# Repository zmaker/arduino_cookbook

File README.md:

# arduino_cookbook
gli sketch del nuovo progetto Arduino Cookbook e dei video di YouTube

La pagina con i video: 
http://www.zeppelinmaker.it/arduino100/

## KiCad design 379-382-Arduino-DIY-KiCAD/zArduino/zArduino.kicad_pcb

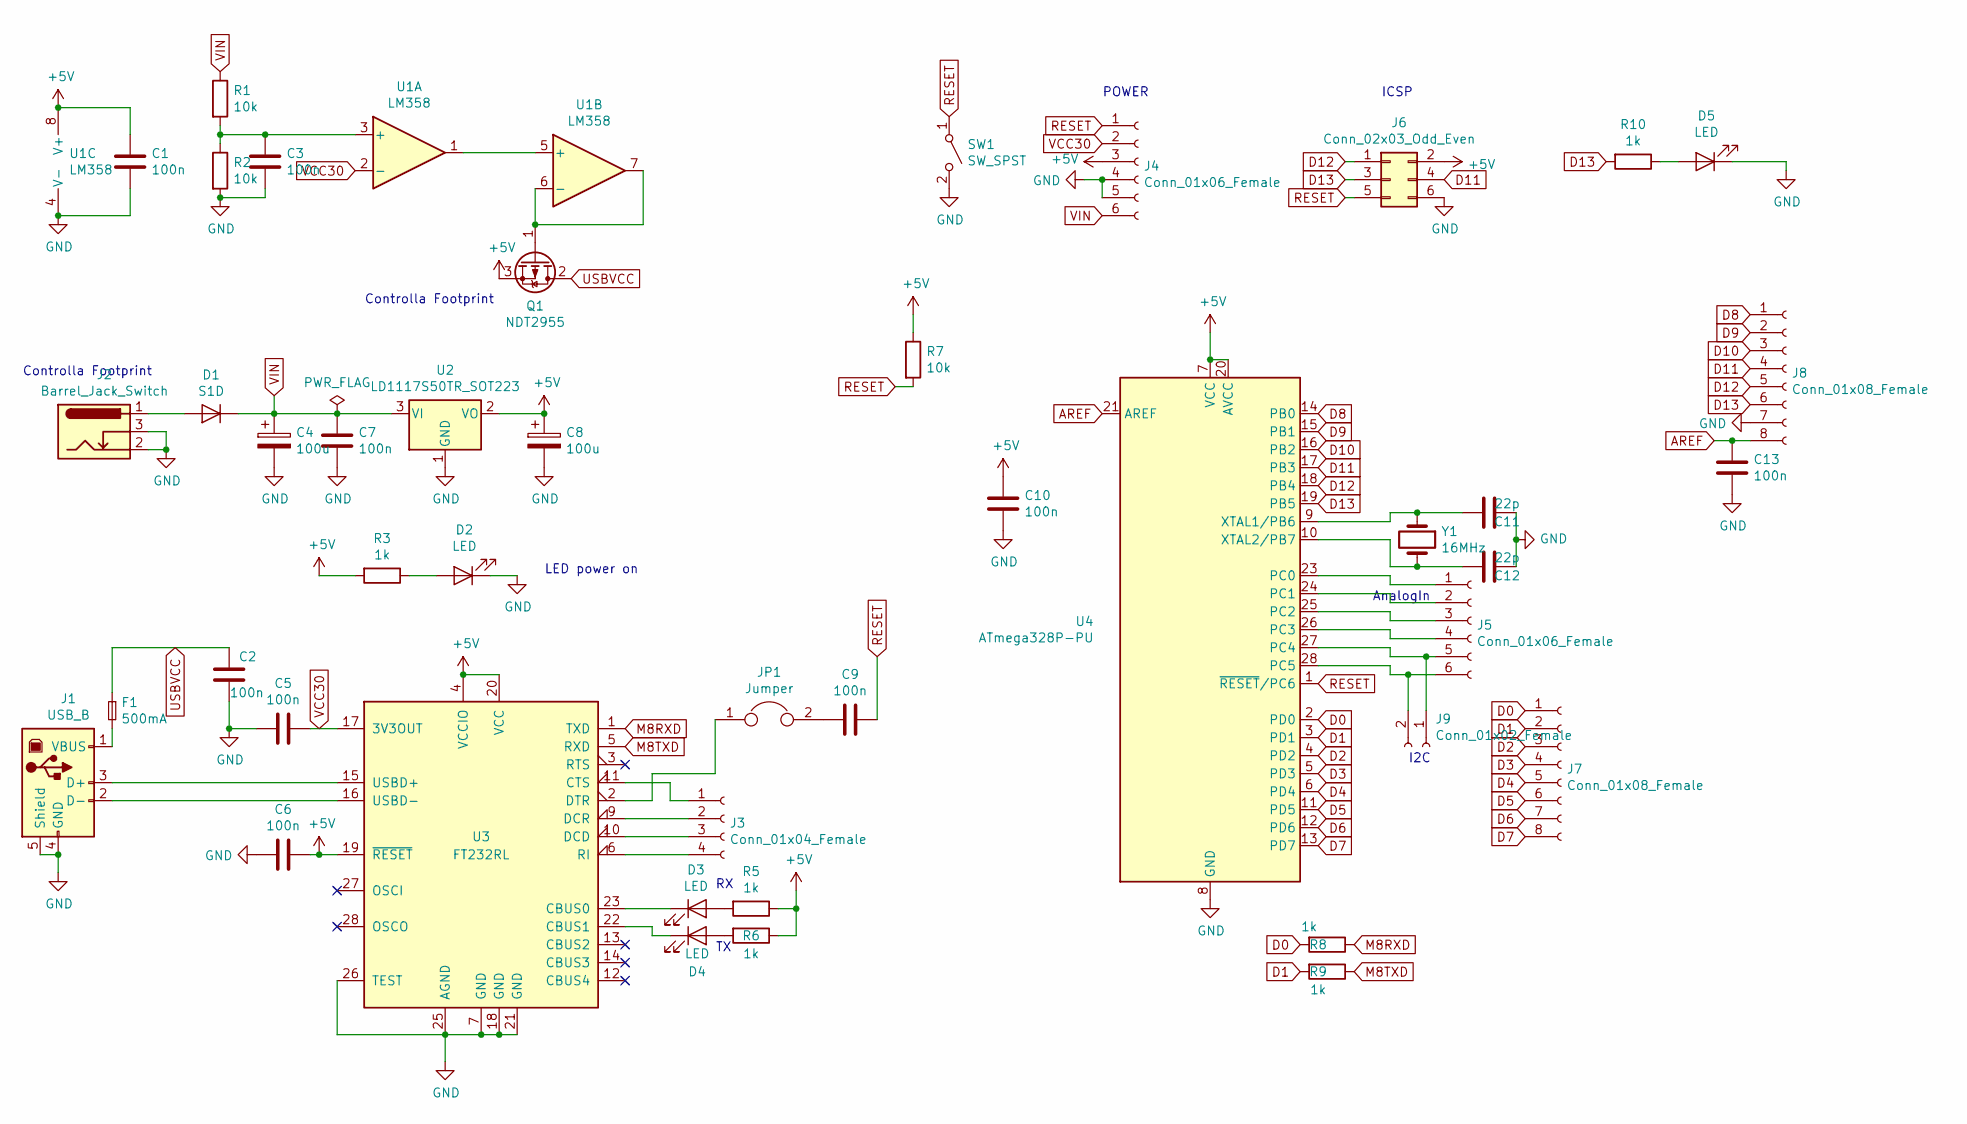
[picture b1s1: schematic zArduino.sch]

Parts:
C1, C2, C3, C5, C6, C7, C9, C10, C13: 100n; C_0805_2012Metric_Pad1.15x1.40mm_HandSolder
C4, C8: 100u; CP_Elec_8x6.2
C11, C12: 22p; C_0805_2012Metric_Pad1.15x1.40mm_HandSolder
D1: S1D; D_SMA_Handsoldering
D2, D3, D4, D5: LED; LED_1206_3216Metric_Pad1.42x1.75mm_HandSolder
F1: 500mA; Fuse_1206_3216Metric_Pad1.42x1.75mm_HandSolder
J1: USB_B; USB_B_OST_USB-B1HSxx_Horizontal
J2: Barrel_Jack_Switch; BarrelJack_Wuerth_6941xx301002
J3: Conn_01x04_Female; PinHeader_1x04_P2.54mm_Vertical
J4, J5: Conn_01x06_Female; PinHeader_1x06_P2.54mm_Vertical
J6: Conn_02x03_Odd_Even; PinHeader_2x03_P2.54mm_Vertical
J7, J8: Conn_01x08_Female; PinHeader_1x08_P2.54mm_Vertical
J9: Conn_01x02_Female; PinHeader_1x02_P2.54mm_Vertical
JP1: Jumper; PinHeader_1x02_P2.54mm_Vertical
Q1: NDT2955; SOT-223-3_TabPin2
R1, R2, R7: 10k; R_0805_2012Metric_Pad1.15x1.40mm_HandSolder
R3, R5, R6, R8, R9, R10: 1k; R_0805_2012Metric_Pad1.15x1.40mm_HandSolder
SW1: SW_SPST; SW_Push_1P1T_NO_CK_KSC7xxJ
U1: LM358; SOIC-8_5.275x5.275mm_P1.27mm
U2: LD1117S50TR_SOT223; TO-252-2
U3: FT232RL; SSOP-28_5.3x10.2mm_P0.65mm
U4: ATmega328P-PU; DIP-28_W7.62mm
Y1: 16MHz; Crystal_SMD_HC49-SD

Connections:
+5V: C1.1, C6.1, C8.1, C10.1, J4.3, J6.2, Q1.3 (S), R3.2, R5.1, R6.1, R7.1, U1.8 (V+), U2.2 (VO), U3.4 (VCCIO), U3.19 (~RESET~), U3.20 (VCC), U4.7 (VCC), U4.20 (AVCC)
AREF: C13.1, J8.8, U4.21 (AREF)
D0: J7.1, R8.2, U4.2 (PD0)
D1: J7.2, R9.2, U4.3 (PD1)
D2: J7.3, U4.4 (PD2)
D3: J7.4, U4.5 (PD3)
D4: J7.5, U4.6 (PD4)
D5: J7.6, U4.11 (PD5)
D6: J7.7, U4.12 (PD6)
D7: J7.8, U4.13 (PD7)
D8: J8.1, U4.14 (PB0)
D9: J8.2, U4.15 (PB1)
D10: J8.3, U4.16 (PB2)
D11: J6.4, J8.4, U4.17 (PB3)
D12: J6.1, J8.5, U4.18 (PB4)
D13: J6.3, J8.6, R10.2, U4.19 (PB5)
GND: C1.2, C2.2, C3.2, C4.2, C5.2, C6.2, C7.2, C8.2, C10.2, C11.1, C12.1, C13.2, D2.1 (K), D5.1 (K), J1.4 (GND), J1.5 (Shield), J2.2, J2.3, J4.4, J4.5, J6.6, J8.7, R2.2, SW1.2 (B), U1.4 (V-), U2.1 (GND), U3.7 (GND), U3.18 (GND), U3.21 (GND), U3.25 (AGND), U3.26 (TEST), U4.8 (GND), U4.22 (GND)
M8RXD: R8.1, U3.1 (TXD)
M8TXD: R9.1, U3.5 (RXD)
unnamed: C3.1, R1.2, R2.1, U1.3 (+)
unnamed: C9.2, JP1.2
unnamed: C11.2, U4.9 (XTAL1/PB6), Y1.1
unnamed: C12.2, U4.10 (XTAL2/PB7), Y1.2
unnamed: D1.2 (A), J2.1
unnamed: D2.2 (A), R3.1
unnamed: D3.1 (K), U3.23 (CBUS0)
unnamed: D3.2 (A), R5.2
unnamed: D4.1 (K), U3.22 (CBUS1)
unnamed: D4.2 (A), R6.2
unnamed: D5.2 (A), R10.1
unnamed: F1.2, J1.1 (VBUS)
unnamed: J1.2 (D-), U3.16 (USBD-)
unnamed: J1.3 (D+), U3.15 (USBD+)
unnamed: J3.1, U3.11 (CTS)
unnamed: J3.2, U3.9 (DCR)
unnamed: J3.3, U3.10 (DCD)
unnamed: J3.4, U3.6 (RI)
unnamed: J5.1, U4.23 (PC0)
unnamed: J5.2, U4.24 (PC1)
unnamed: J5.3, U4.25 (PC2)
unnamed: J5.4, U4.26 (PC3)
unnamed: J5.5, J9.1, U4.27 (PC4)
unnamed: J5.6, J9.2, U4.28 (PC5)
unnamed: JP1.1, U3.2 (DTR)
unnamed: Q1.1 (G), U1.6 (-), U1.7
unnamed 45: U3.3 (RTS); also elsewhere on the board
unnamed: U1.1, U1.5 (+)
RESET: C9.1, J4.1, J6.5, R7.2, SW1.1 (A), U4.1 (~RESET~/PC6); also elsewhere on the board
USBVCC: C2.1, F1.1, Q1.2 (D)
VCC30: C5.1, J4.2, U1.2 (-), U3.17 (3V3OUT)
VIN: C4.1, C7.1, D1.1 (K), J4.6, R1.1, U2.3 (VI)

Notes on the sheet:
Controlla Footprint
LED power on
POWER
ICSP
AnalogIn
I2C

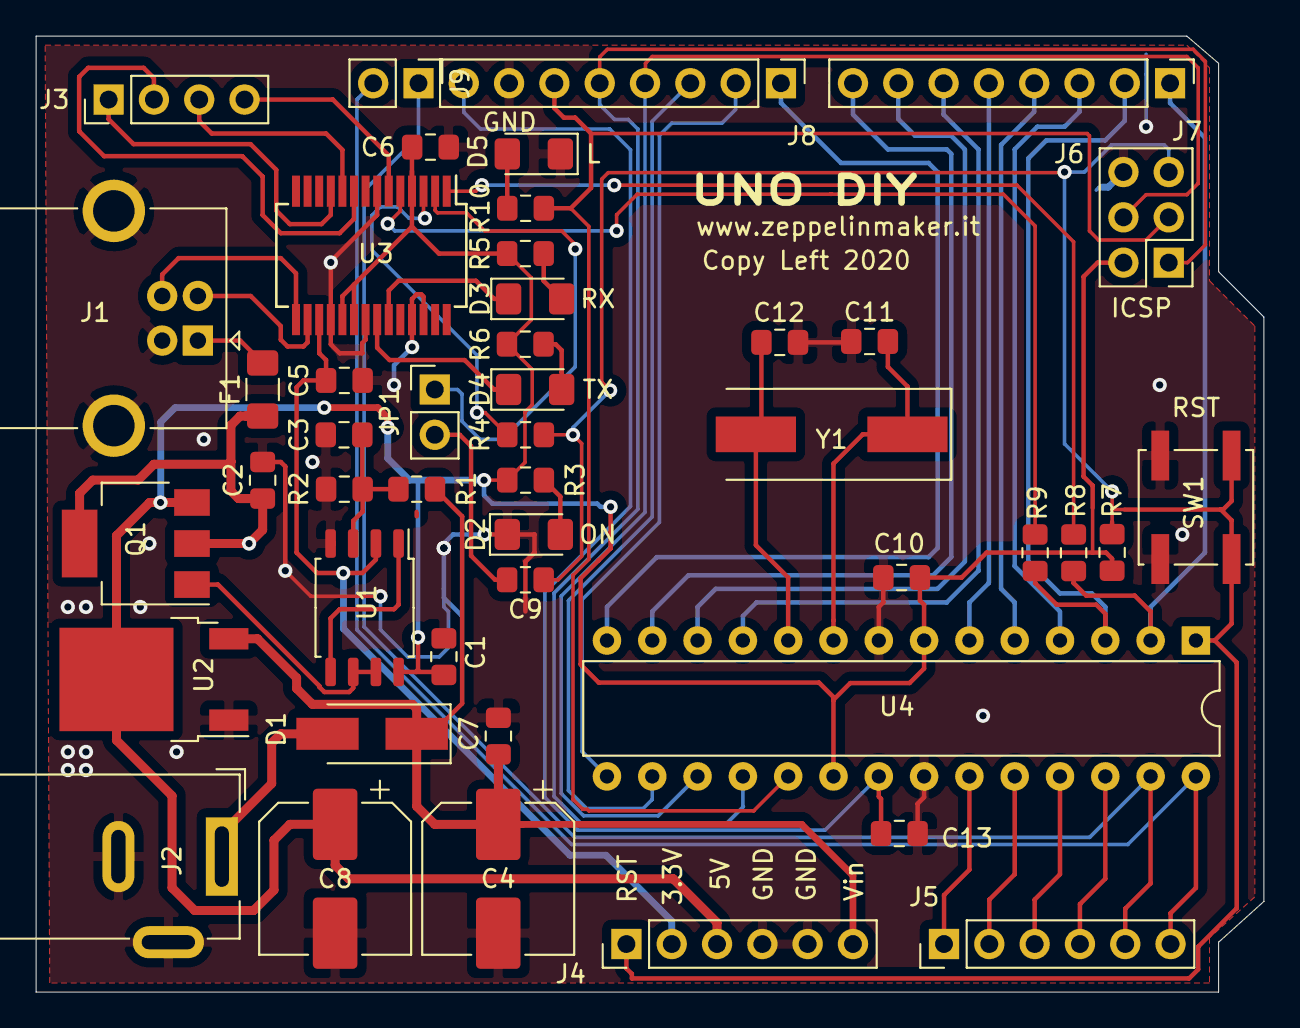
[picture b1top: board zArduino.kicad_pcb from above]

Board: 2 copper layers, 68.8 x 53.6 mm, 46 parts (0 on the bottom side), 51 nets.

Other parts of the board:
R4: 1k; R_0805_2012Metric_Pad1.15x1.40mm_HandSolder

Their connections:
unnamed 45: R4.2; also elsewhere on the board
RESET: R4.1; also elsewhere on the board

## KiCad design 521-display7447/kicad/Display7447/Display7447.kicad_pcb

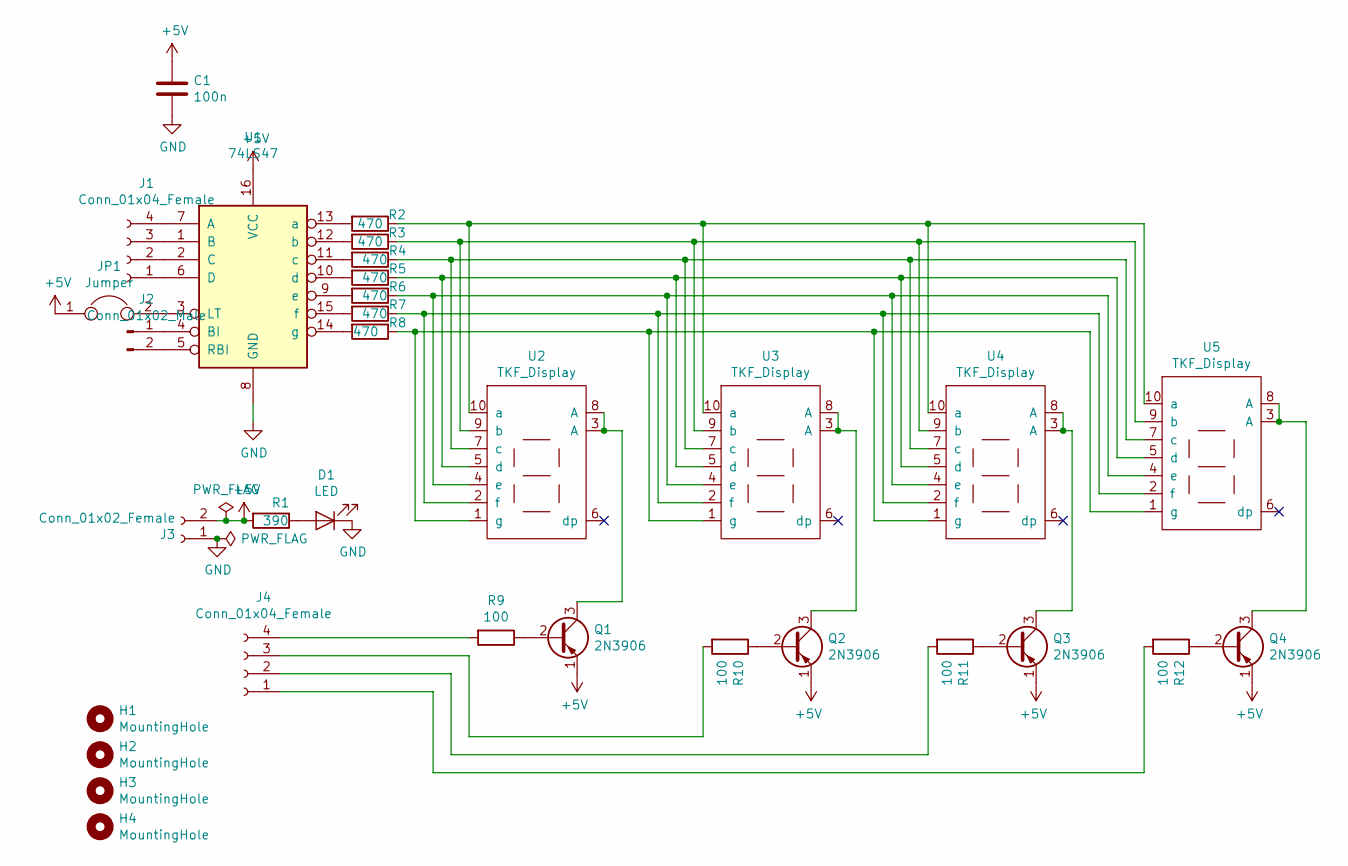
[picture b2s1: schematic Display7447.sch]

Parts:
C1: 100n; C_Disc_D5.0mm_W2.5mm_P2.50mm
D1: LED; LED_D5.0mm
H1, H2, H3, H4: MountingHole; MountingHole_3.2mm_M3
J1, J4: Conn_01x04_Female; PinSocket_1x04_P2.54mm_Vertical
J2: Conn_01x02_Male; PinSocket_1x02_P2.54mm_Vertical
J3: Conn_01x02_Female; PinSocket_1x02_P2.54mm_Vertical
JP1: Jumper; PinSocket_2x01_P2.54mm_Vertical
Q1, Q2, Q3, Q4: 2N3906; TO-92_Inline
R1: 390; R_Axial_DIN0204_L3.6mm_D1.6mm_P7.62mm_Horizontal
R2, R3, R4, R5, R6, R7, R8: 470; R_Axial_DIN0204_L3.6mm_D1.6mm_P7.62mm_Horizontal
R9, R10, R11, R12: 100; R_Axial_DIN0204_L3.6mm_D1.6mm_P7.62mm_Horizontal
U1: 74LS47; DIP-16_W7.62mm_Socket_LongPads
U2, U3, U4, U5: TKF_Display; TFK-Display

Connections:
+5V: C1.1, J3.2, JP1.1, Q1.1 (E), Q2.1 (E), Q3.1 (E), Q4.1 (E), R1.2, U1.16 (VCC)
GND: C1.2, D1.1 (K), J3.1, U1.8 (GND)
unnamed: D1.2 (A), R1.1
unnamed: J1.1, U1.6 (D)
unnamed: J1.2, U1.2 (C)
unnamed: J1.3, U1.1 (B)
unnamed: J1.4, U1.7 (A)
unnamed: J2.1, U1.4 (BI)
unnamed: J2.2, U1.5 (RBI)
unnamed: J4.1, R12.2
unnamed: J4.2, R11.2
unnamed: J4.3, R10.2
unnamed: J4.4, R9.2
unnamed: JP1.2, U1.3 (LT)
unnamed: Q1.2 (B), R9.1
unnamed: Q1.3 (C), U2.3 (A), U2.8 (A)
unnamed: Q2.2 (B), R10.1
unnamed: Q2.3 (C), U3.3 (A), U3.8 (A)
unnamed: Q3.2 (B), R11.1
unnamed: Q3.3 (C), U4.3 (A), U4.8 (A)
unnamed: Q4.2 (B), R12.1
unnamed: Q4.3 (C), U5.3 (A), U5.8 (A)
unnamed: R2.1, U2.10 (a), U3.10 (a), U4.10 (a), U5.10 (a)
unnamed: R2.2, U1.13 (a)
unnamed: R3.1, U2.9 (b), U3.9 (b), U4.9 (b), U5.9 (b)
unnamed: R3.2, U1.12 (b)
unnamed: R4.1, U2.7 (c), U3.7 (c), U4.7 (c), U5.7 (c)
unnamed: R4.2, U1.11 (c)
unnamed: R5.1, U2.5 (d), U3.5 (d), U4.5 (d), U5.5 (d)
unnamed: R5.2, U1.10 (d)
unnamed: R6.1, U2.4 (e), U3.4 (e), U4.4 (e), U5.4 (e)
unnamed: R6.2, U1.9 (e)
unnamed: R7.1, U2.2 (f), U3.2 (f), U4.2 (f), U5.2 (f)
unnamed: R7.2, U1.15 (f)
unnamed: R8.1, U2.1 (g), U3.1 (g), U4.1 (g), U5.1 (g)
unnamed: R8.2, U1.14 (g)

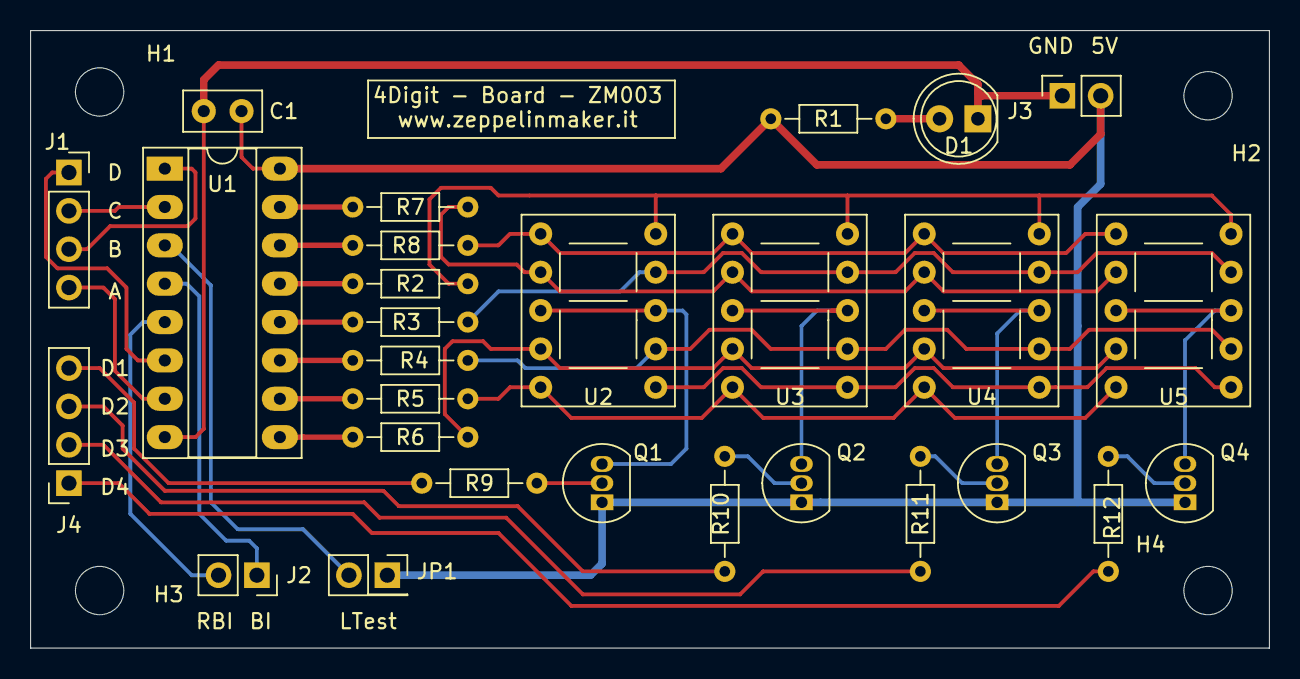
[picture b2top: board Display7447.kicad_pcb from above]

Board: 2 copper layers, 82.0 x 40.9 mm, 32 parts (0 on the bottom side), 36 nets.

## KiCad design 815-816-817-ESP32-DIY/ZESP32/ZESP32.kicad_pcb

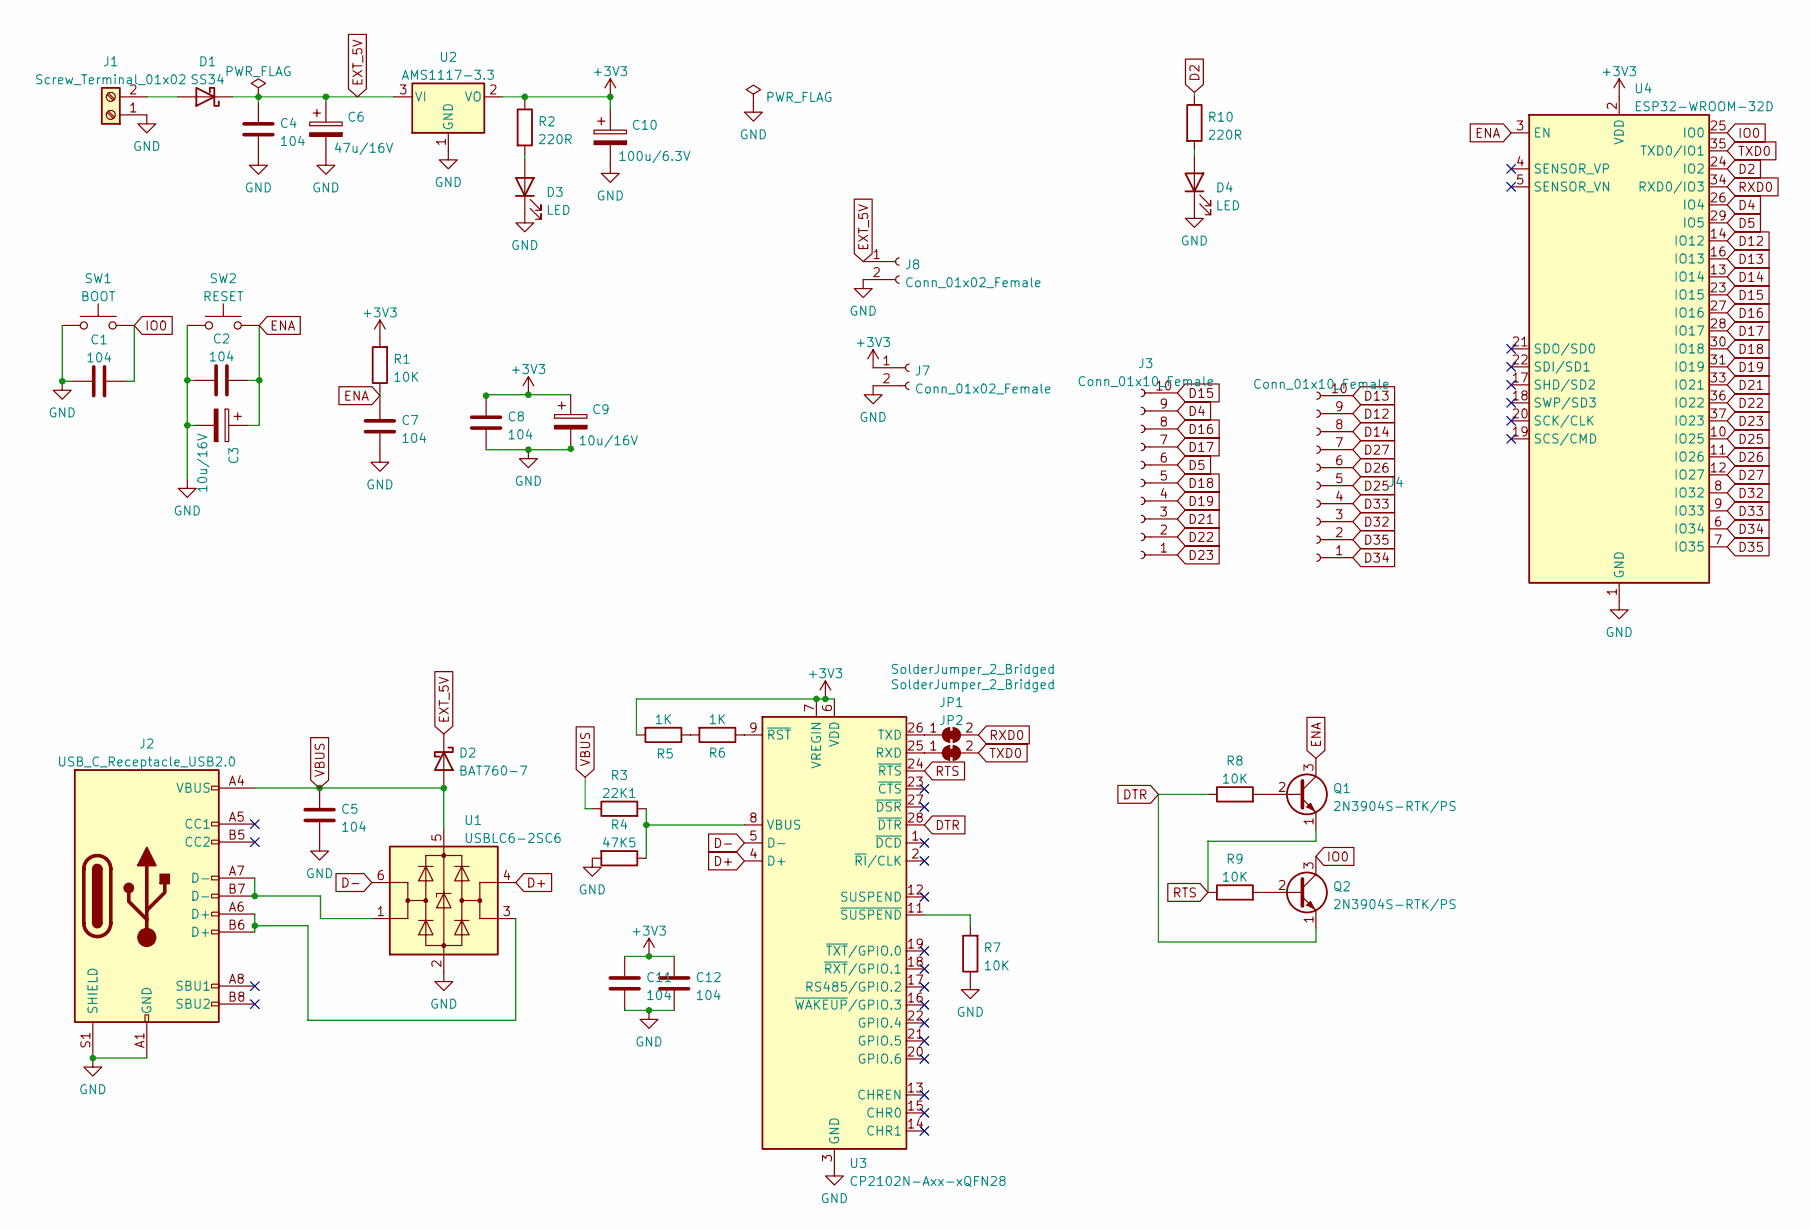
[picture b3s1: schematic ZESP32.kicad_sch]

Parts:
C1, C2, C4, C5, C7, C8, C11, C12: 104; C_0805_2012Metric_Pad1.18x1.45mm_HandSolder
C3, C9: 10u/16V; CP_Elec_4x5.4
C6: 47u/16V; CP_Elec_5x5.4
C10: 100u/6.3V; CP_Elec_6.3x5.7
D1: SS34; D_SMA
D2: BAT760-7; D_SOD-323F
D3, D4: LED; LED_0805_2012Metric
J1: Screw_Terminal_01x02; TerminalBlock_bornier-2_P5.08mm
J2: USB_C_Receptacle_USB2.0; USB_C_Receptacle_HRO_TYPE-C-31-M-12
J3, J4: Conn_01x10_Female; PinHeader_1x10_P2.54mm_Vertical
J7, J8: Conn_01x02_Female; PinHeader_1x02_P2.54mm_Vertical
JP1, JP2: SolderJumper_2_Bridged; SolderJumper-2_P1.3mm_Bridged_RoundedPad1.0x1.5mm
Q1, Q2: 2N3904S-RTK/PS; SOT-23-3-REV
R1, R7, R8, R9: 10K; R_0805_2012Metric_Pad1.20x1.40mm_HandSolder
R2, R10: 220R; R_0805_2012Metric_Pad1.20x1.40mm_HandSolder
R3: 22K1; R_0805_2012Metric_Pad1.20x1.40mm_HandSolder
R4: 47K5; R_0805_2012Metric_Pad1.20x1.40mm_HandSolder
R5, R6: 1K; R_0805_2012Metric_Pad1.20x1.40mm_HandSolder
SW1: BOOT; SW_Push_1P1T_NO_6x6mm_H9.5mm
SW2: RESET; SW_Push_1P1T_NO_6x6mm_H9.5mm
U1: USBLC6-2SC6; SOT-23-6
U2: AMS1117-3.3; SOT-223-3_TabPin2
U3: CP2102N-Axx-xQFN28; QFN-28-1EP_5x5mm_P0.5mm_EP3.35x3.35mm
U4: ESP32-WROOM-32D; ESP32-WROOM-32

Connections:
+3V3: C8.1, C9.1, C10.1, C11.1, C12.1, J7.1, R1.2, R2.1, R5.2, U2.2 (VO), U3.6 (VDD), U3.7 (VREGIN), U4.2 (VDD)
D2: R10.1, U4.24 (IO2)
D4: J3.9, U4.26 (IO4)
D5: J3.6, U4.29 (IO5)
D12: J4.9, U4.14 (IO12)
D13: J4.10, U4.16 (IO13)
D14: J4.8, U4.13 (IO14)
D15: J3.10, U4.23 (IO15)
D16: J3.8, U4.27 (IO16)
D17: J3.7, U4.28 (IO17)
D18: J3.5, U4.30 (IO18)
D19: J3.4, U4.31 (IO19)
D21: J3.3, U4.33 (IO21)
D22: J3.2, U4.36 (IO22)
D23: J3.1, U4.37 (IO23)
D25: J4.5, U4.10 (IO25)
D26: J4.6, U4.11 (IO26)
D27: J4.7, U4.12 (IO27)
D32: J4.3, U4.8 (IO32)
D33: J4.4, U4.9 (IO33)
D34: J4.1, U4.6 (IO34)
D35: J4.2, U4.7 (IO35)
D+: U1.4 (I/O2), U3.4 (D+)
D-: U1.6 (I/O1), U3.5 (D-)
DTR: Q2.1 (E), R8.1, U3.28 (~DTR)
ENA: C2.2, C3.1, C7.1, Q1.3 (C), R1.1, SW2.2, U4.3 (EN)
EXT_5V: C4.1, C6.1, D1.1 (K), D2.1 (K), J8.1, U2.3 (VI)
GND: C1.1, C2.1, C3.2, C4.2, C5.2, C6.2, C7.2, C8.2, C9.2, C10.2, C11.2, C12.2, D3.1 (K), D4.1 (K), J1.1, J2.A1 (GND), J2.A12 (GND), J2.B1 (GND), J2.B12 (GND), J2.S1 (SHIELD), J7.2, J8.2, R4.2, R7.1, SW1.1, SW2.1, U1.2 (GND), U2.1 (GND), U3.3 (GND), U3.29 (GND), U4.1 (GND), U4.15 (GND), U4.38 (GND), U4.39 (GND)
IO0: C1.2, Q2.3 (C), SW1.2, U4.25 (IO0)
unnamed: D1.2 (A), J1.2
unnamed: D3.2 (A), R2.2
unnamed: D4.2 (A), R10.2
unnamed: J2.A6 (D+), J2.B6 (D+), U1.3 (I/O2)
unnamed: J2.A7 (D-), J2.B7 (D-), U1.1 (I/O1)
unnamed: JP1.1 (A), U3.26 (TXD)
unnamed: JP2.1 (A), U3.25 (RXD)
unnamed: Q1.2 (B), R8.2
unnamed: Q2.2 (B), R9.2
unnamed: R3.2, R4.1, U3.8 (VBUS)
unnamed: R5.1, R6.2
unnamed: R6.1, U3.9 (~RST)
unnamed: R7.2, U3.11 (~SUSPEND)
RTS: Q1.1 (E), R9.1, U3.24 (~RTS)
RXD0: JP1.2 (B), U4.34 (RXD0/IO3)
TXD0: JP2.2 (B), U4.35 (TXD0/IO1)
VBUS: C5.1, D2.2 (A), J2.A4 (VBUS), J2.A9 (VBUS), J2.B4 (VBUS), J2.B9 (VBUS), R3.1, U1.5 (VBUS)

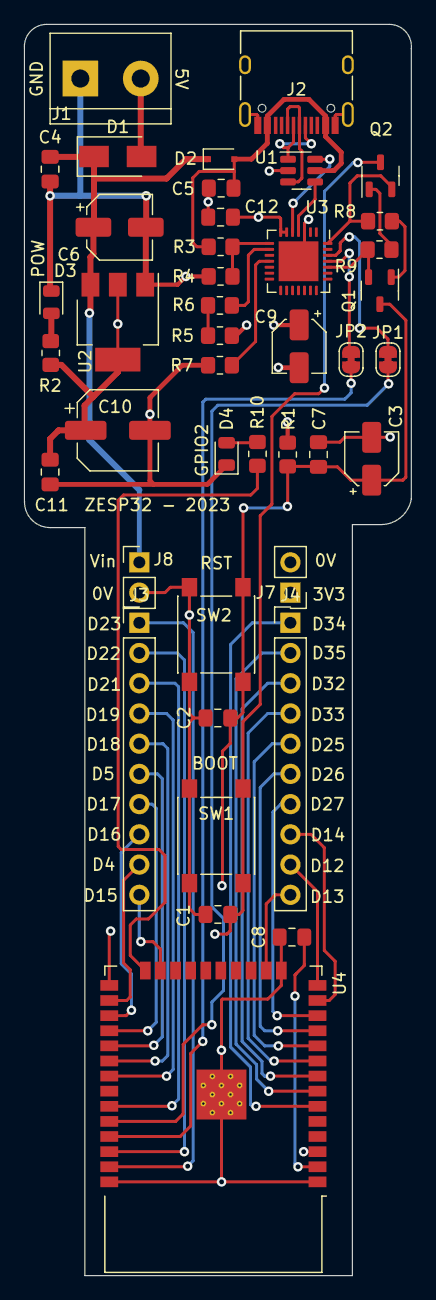
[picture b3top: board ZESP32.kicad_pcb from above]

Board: 4 copper layers, 32.5 x 105.2 mm, 42 parts (0 on the bottom side), 46 nets.

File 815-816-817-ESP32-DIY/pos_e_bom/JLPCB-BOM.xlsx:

Comment | Designator | Footprint | JLCPCB Part #（optional）
100nf | C1, C2, C4, C5, C7, C8, C11, C12 | Capacitor_SMD:C_0805_2012Metric_Pad1.18x1.45mm_HandSolder | C49678
10u/16V | C3, C9 | Capacitor_SMD:CP_Elec_4x5.4 | C3001198
47u/16V | C6 | Capacitor_SMD:CP_Elec_5x5.4 | C72515
100u/6.3V | C10 | Capacitor_SMD:CP_Elec_6.3x5.7 | C65235
SS34 | D1 | Diode_SMD:D_SMA | C8678
BAT760-7 | D2 | Diode_SMD:D_SOD-323F | C124187
LED | D3, D4 | LED_SMD:LED_0805_2012Metric | C2297
Screw_Terminal_01x02 | J1 | TerminalBlock:TerminalBlock_bornier-2_P5.08mm
USB_C_Receptacle_USB2.0 | J2 | Connector_USB:USB_C_Receptacle_HRO_TYPE-C-31-M-12 | C167321
Conn_01x10_Female | J3, J4 | Connector_PinHeader_2.54mm:PinHeader_1x10_P2.54mm_Vertical
Conn_01x02_Female | J7, J8 | Connector_PinHeader_2.54mm:PinHeader_1x02_P2.54mm_Vertical
SolderJumper_2_Bridged | JP1, JP2 | Jumper:SolderJumper-2_P1.3mm_Bridged_RoundedPad1.0x1.5mm
2N3904S-RTK/PS | Q1, Q2 | Package_TO_SOT_SMD:SOT-23-3-REV | C18536
10K | R1, R7, R8, R9 | Resistor_SMD:R_0805_2012Metric_Pad1.20x1.40mm_HandSolder | C864029
220R | R2, R10 | Resistor_SMD:R_0805_2012Metric_Pad1.20x1.40mm_HandSolder | C844830
22K1 | R3 | Resistor_SMD:R_0805_2012Metric_Pad1.20x1.40mm_HandSolder | C865310
47K5 | R4 | Resistor_SMD:R_0805_2012Metric_Pad1.20x1.40mm_HandSolder | C245335
1K | R5, R6 | Resistor_SMD:R_0805_2012Metric_Pad1.20x1.40mm_HandSolder | C844821
BOOT | SW1 | Button_Switch_SMD:SW_Push_1P1T_NO_6x6mm_H9.5mm | C255812
RESET | SW2 | Button_Switch_SMD:SW_Push_1P1T_NO_6x6mm_H9.5mm | C255812
USBLC6-2SC6 | U1 | Package_TO_SOT_SMD:SOT-23-6 | C2827654
AMS1117-3.3 | U2 | Package_TO_SOT_SMD:SOT-223-3_TabPin2 | C6186
CP2102N-Axx-xQFN28 | U3 | Package_DFN_QFN:QFN-28-1EP_5x5mm_P0.5mm_EP3.35x3.35mm | C964632
ESP32-WROOM-32D | U4 | RF_Module:ESP32-WROOM-32 | C473012

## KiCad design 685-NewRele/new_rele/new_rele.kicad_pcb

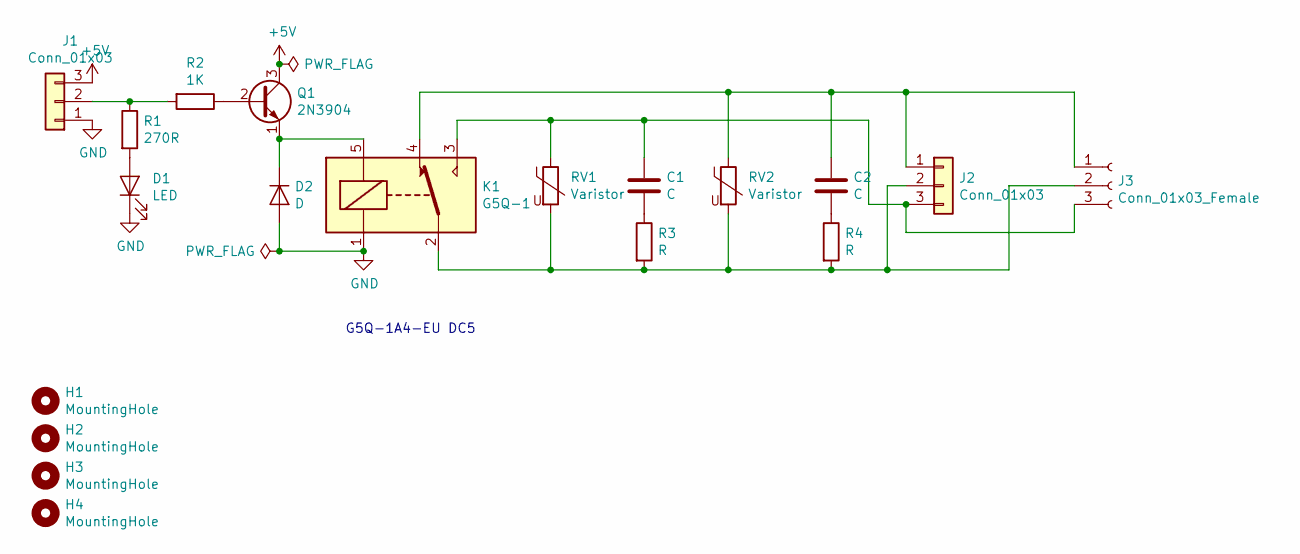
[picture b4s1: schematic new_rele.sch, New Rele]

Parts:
C1, C2: C; C_Disc_D7.5mm_W2.5mm_P5.00mm
D1: LED; LED_D5.0mm
D2: D; D_DO-41_SOD81_P10.16mm_Horizontal
H1, H2, H3, H4: MountingHole; MountingHole_3.2mm_M3
J1: Conn_01x03; PinSocket_1x03_P2.54mm_Vertical
J2: Conn_01x03; TerminalBlock_bornier-3_P5.08mm
J3: Conn_01x03_Female; PinSocket_1x03_P2.54mm_Vertical
K1: G5Q-1; Relay_SPDT_Omron-G5Q-1
Q1: 2N3904; TO-92_HandSolder
R1: 270R; R_Axial_DIN0207_L6.3mm_D2.5mm_P7.62mm_Horizontal
R2: 1K; R_Axial_DIN0207_L6.3mm_D2.5mm_P7.62mm_Horizontal
R3, R4: R; R_Axial_DIN0207_L6.3mm_D2.5mm_P7.62mm_Horizontal
RV1, RV2: Varistor; RV_Disc_D7mm_W4.2mm_P5mm

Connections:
+5V: J1.3, Q1.3 (C)
GND: D1.1 (K), D2.2 (A), J1.1, K1.1
unnamed: C1.1, J2.3, J3.3, K1.3, RV1.1
unnamed: C1.2, R3.1
unnamed: C2.1, J2.1, J3.1, K1.4, RV2.1
unnamed: C2.2, R4.1
unnamed: D1.2 (A), R1.2
unnamed: D2.1 (K), K1.5, Q1.1 (E)
unnamed: J1.2, R1.1, R2.2
unnamed: J2.2, J3.2, K1.2, R3.2, R4.2, RV1.2, RV2.2
unnamed: Q1.2 (B), R2.1

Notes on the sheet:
G5Q-1A4-EU DC5

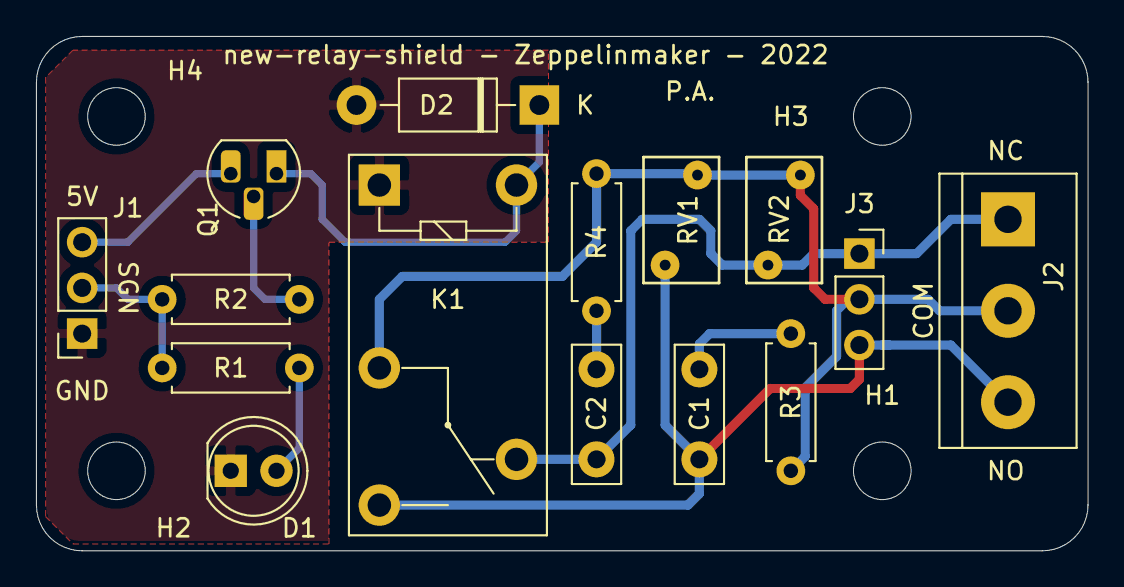
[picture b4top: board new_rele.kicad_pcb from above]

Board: 2 copper layers, 58.4 x 28.6 mm, 19 parts (0 on the bottom side), 11 nets.

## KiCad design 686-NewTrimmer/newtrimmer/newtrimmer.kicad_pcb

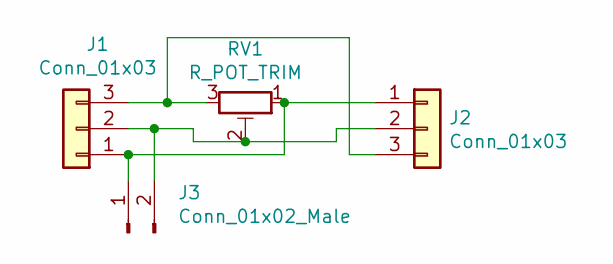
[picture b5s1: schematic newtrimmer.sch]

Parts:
J1, J2: Conn_01x03; PinSocket_1x03_P2.54mm_Vertical
J3: Conn_01x02_Male; PinHeader_1x02_P2.54mm_Vertical
RV1: R_POT_TRIM; Potentiometer_Piher_PT-10-V05_Vertical

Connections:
unnamed: J1.1, J2.1, J3.1, RV1.1
unnamed: J1.2, J2.2, J3.2, RV1.2
unnamed: J1.3, J2.3, RV1.3

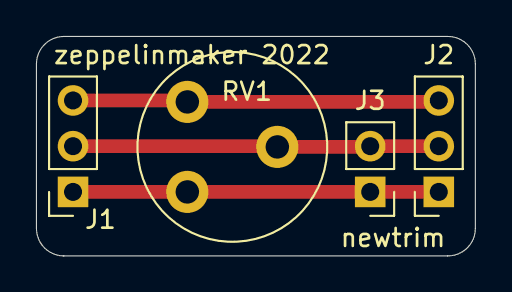
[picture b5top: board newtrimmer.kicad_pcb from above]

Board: 2 copper layers, 24.4 x 12.2 mm, 4 parts (0 on the bottom side), 3 nets.

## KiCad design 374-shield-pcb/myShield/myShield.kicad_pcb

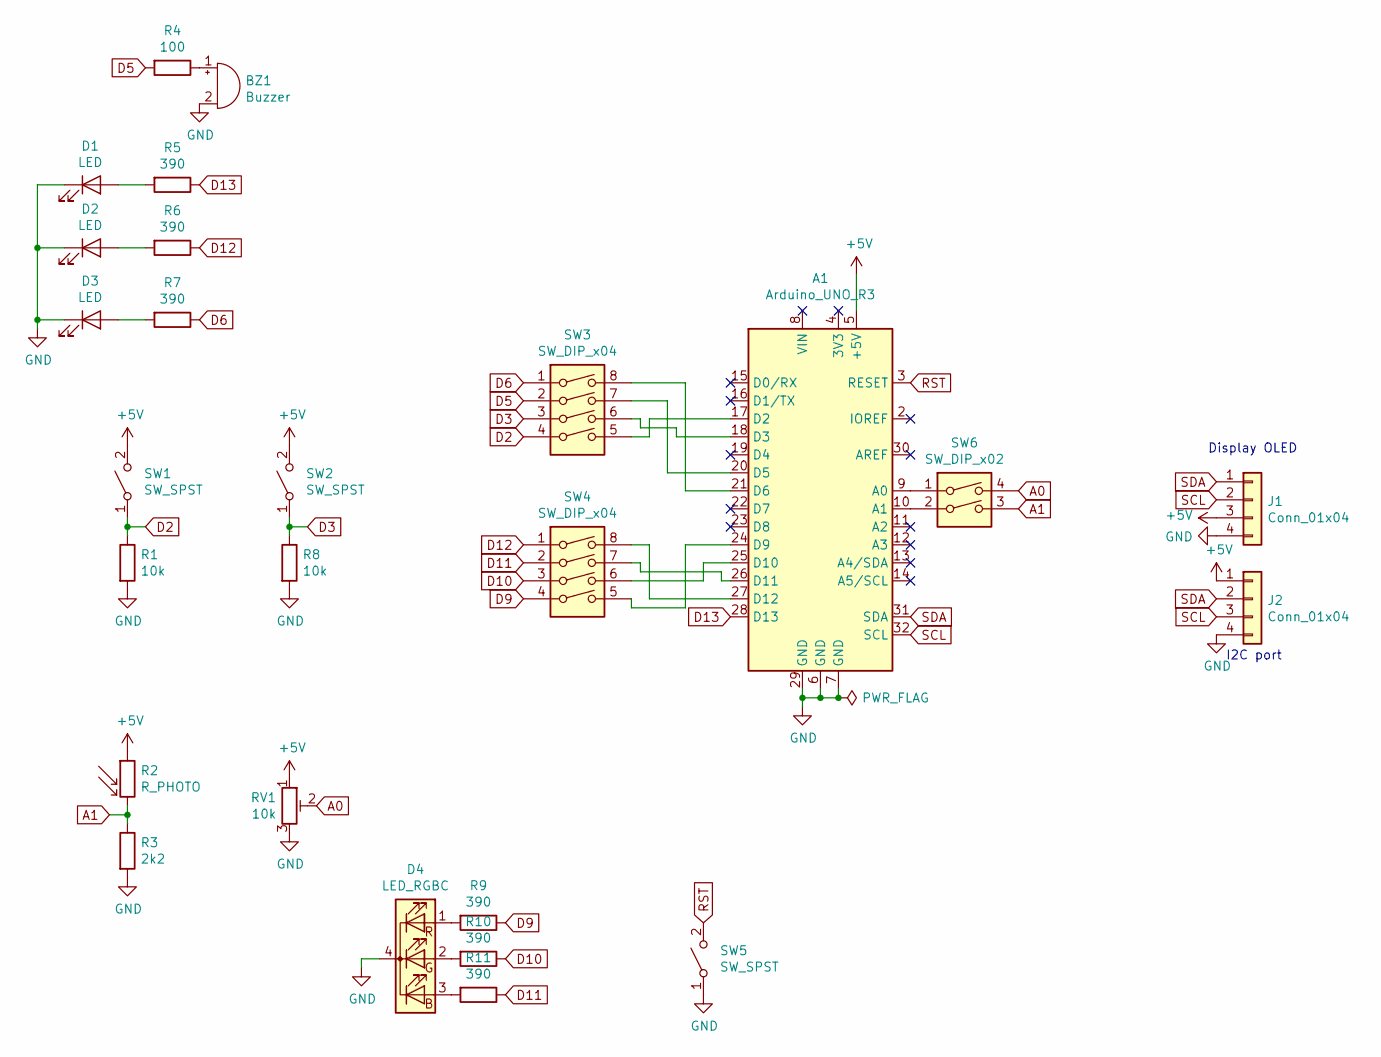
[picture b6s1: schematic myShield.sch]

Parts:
A1: Arduino_UNO_R3
BZ1: Buzzer; Buzzer_12x9.5RM7.6
D1, D2, D3: LED; LED_D5.0mm
D4: LED_RGBC; RGB-LED
J1, J2: Conn_01x04; PinSocket_1x04_P2.54mm_Vertical
R1, R8: 10k; R_Axial_DIN0207_L6.3mm_D2.5mm_P10.16mm_Horizontal
R2: R_PHOTO; R_LDR_4.9x4.2mm_P2.54mm_Vertical
R3: 2k2; R_Axial_DIN0207_L6.3mm_D2.5mm_P10.16mm_Horizontal
R4: 100; R_Axial_DIN0207_L6.3mm_D2.5mm_P10.16mm_Horizontal
R5, R6, R7, R9, R10, R11: 390; R_Axial_DIN0207_L6.3mm_D2.5mm_P10.16mm_Horizontal
RV1: 10k; Potentiometer_ACP_CA9-V10_Vertical
SW1, SW2, SW5: SW_SPST; SW_PUSH_6mm
SW3, SW4: SW_DIP_x04; SW_DIP_SPSTx04_Slide_6.7x11.72mm_W7.62mm_P2.54mm_LowProfile
SW6: SW_DIP_x02; SW_DIP_SPSTx02_Slide_6.7x6.64mm_W7.62mm_P2.54mm_LowProfile

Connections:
+5V: A1.5 (+5V), J1.3, J2.1, R2.1, RV1.1, SW1.2 (B), SW2.2 (B)
A0: RV1.2, SW6.4
A1: R2.2, R3.1, SW6.3
D2: R1.1, SW1.1 (A), SW3.4
D3: R8.1, SW2.1 (A), SW3.3
D5: R4.2, SW3.2
D6: R7.1, SW3.1
D9: R9.1, SW4.4
D10: R10.1, SW4.3
D11: R11.1, SW4.2
D12: R6.1, SW4.1
D13: A1.28 (D13), R5.1
GND: A1.6 (GND), A1.7 (GND), A1.29 (GND), BZ1.2 (+), D1.1 (K), D2.1 (K), D3.1 (K), D4.4 (K), J1.4, J2.4, R1.2, R3.2, R8.2, RV1.3, SW5.1 (A)
unnamed: A1.9 (A0), SW6.1
unnamed: A1.10 (A1), SW6.2
unnamed: A1.17 (D2), SW3.5
unnamed: A1.18 (D3), SW3.6
unnamed: A1.20 (D5), SW3.7
unnamed: A1.21 (D6), SW3.8
unnamed: A1.24 (D9), SW4.5
unnamed: A1.25 (D10), SW4.6
unnamed: A1.26 (D11), SW4.7
unnamed: A1.27 (D12), SW4.8
unnamed: BZ1.1 (-), R4.1
unnamed: D1.2 (A), R5.2
unnamed: D2.2 (A), R6.2
unnamed: D3.2 (A), R7.2
unnamed: D4.1 (RA), R9.2
unnamed: D4.2 (GA), R10.2
unnamed: D4.3 (BA), R11.2
RST: A1.3 (RESET), SW5.2 (B)
SCL: A1.32 (SCL), J1.2, J2.3
SDA: A1.31 (SDA), J1.1, J2.2

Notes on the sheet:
Display OLED
I2C port

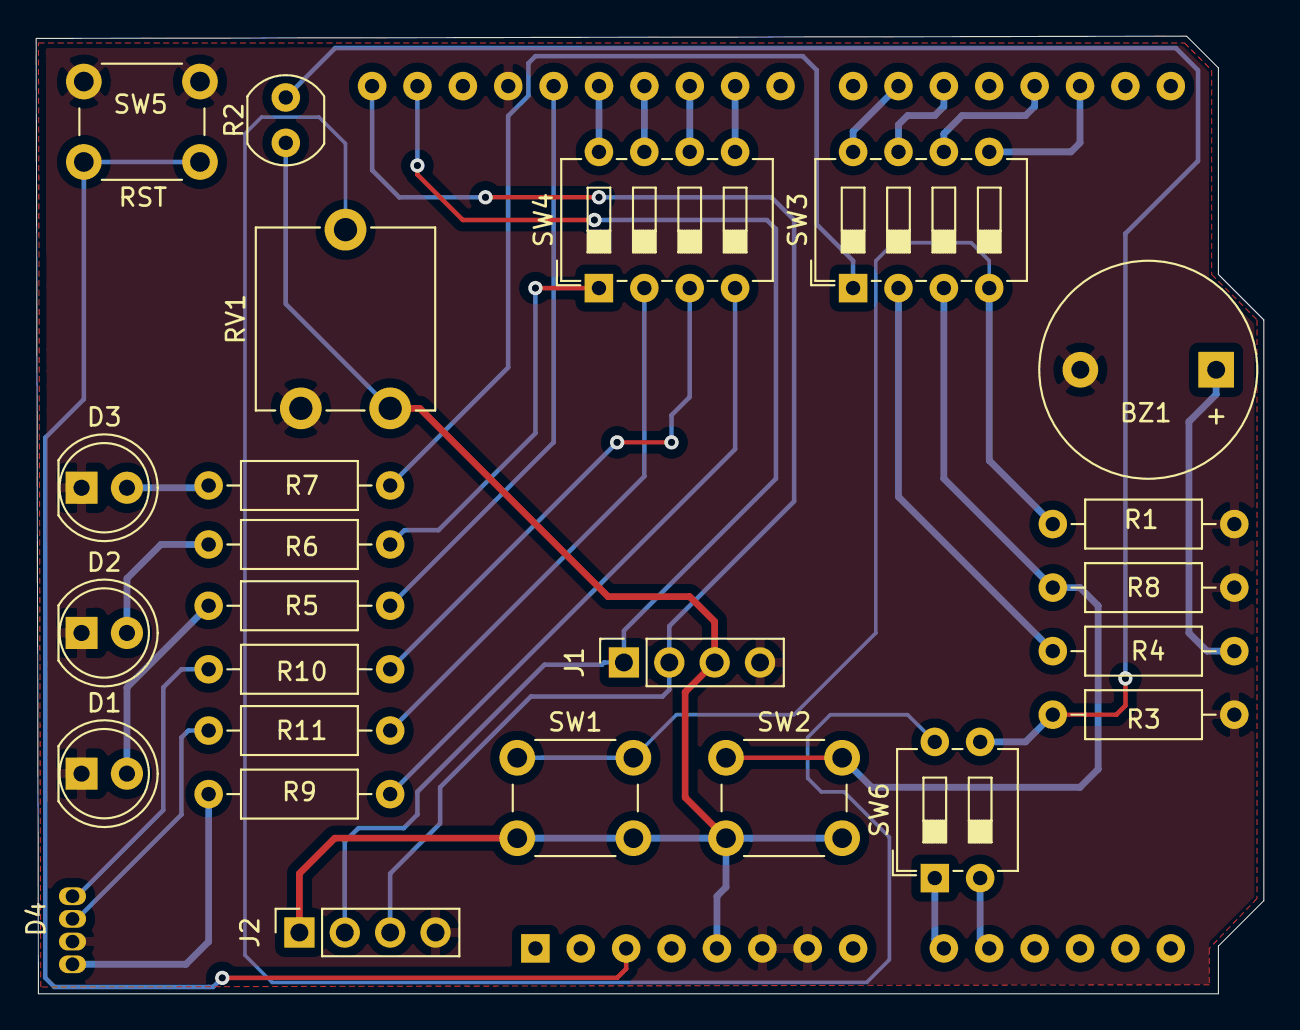
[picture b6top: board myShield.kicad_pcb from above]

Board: 2 copper layers, 68.7 x 53.6 mm, 26 parts (1 on the bottom side), 33 nets.

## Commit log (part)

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2018-06-26 045, 46 e 47
2018-06-27 fix sketch vecchi
2018-06-27 fix sketch vecchi - del folder
2018-07-04 sketch fino a 060
2018-07-05 013 fix
2018-07-05 013 fix 2
2018-07-05 019 fix 2
2018-07-05 021 fix
2018-07-05 021 fix 2
2018-07-05 fix pubb pagina 100
2018-07-06 nuovi sketch 5 luglio
2018-07-16 070-086
2018-07-24 087-99
2018-08-23 fix mouse
2018-08-27 101-109
2018-08-28 rm tensione
2018-09-05 to 122
2018-09-18 123 - 137
2018-10-01 finao a 148
2018-10-15 144-146
2018-10-22 fino al 150
2018-10-29 fino al 155
2018-11-11 fino al 160
2018-11-29 fino a 167 - robot kit
2018-12-18 kit robot
2019-01-28 mkr 1010
2019-02-06 MKR e blynk
2019-02-15 blynk
2019-02-24 blynk-p2
2019-02-28 blynk - 195
2019-03-10 oled
2019-04-09 9 aprile
2019-04-11 11aprile
2019-04-19 fine aprile
2019-05-01 maggio
2019-05-12 termocoppia
2019-05-18 220-224
2019-06-03 rs485
2019-06-14 14-06
2019-06-25 i2c portexpander
2019-06-30 fine giugno
2019-07-03 rainsensor
2019-07-04 test bt
2019-07-22 fine luglio
2019-07-29 fino a 92
2019-08-27 26 agosto
2019-08-30 video settembre
2019-09-03 sleep
2019-09-04 rm file
2019-09-04 257 rm
2019-09-14 meta settembre
2019-09-25 sett-ott
2019-10-04 ottobre
2019-10-17 temp control
2019-10-21 parcheggio
2019-10-24 robot
2019-10-24 robot line
2019-11-13 arduino nov
2019-11-15 neopixel
2019-11-25 fine nov
2019-11-26 semafori
2019-12-08 nov 3nd
2019-12-12 serra
2019-12-20 fasori elettr
2019-12-21 natale
2020-01-06 lcd touch
2020-01-16 ardu calc
2020-01-16 ardu calc 2
2020-01-17 pwm e rele
2020-01-29 dht22
2020-01-31 ds multi
2020-02-18 meta febb
2020-02-26 modbus
2020-03-19 fine marzo
2020-03-23 con cover
2020-03-31 powershield
2020-04-06 peristaltica
2020-04-16 neurali
2020-04-16 fix nnet
2020-04-22 nnet
2020-05-09 maggio 2020 1
2020-06-01 fix define - sketch 090
2020-06-15 morse
2020-06-27 shield
2020-07-02 arduino diy
2020-07-20 bt e appinventor
2020-08-03 errore nome cartelle arduino
2020-08-11 fino a meta settembre
2020-09-17 fino a fine settembre
2020-09-25 fix numeri progetti
2020-10-18 meta ottobre
2020-11-12 novembre
2020-12-14 dec 2020
2021-01-01 jan 2021
2021-01-04 jan 2021 2
2021-01-23 jan 2021 3
2021-01-23 jan 2021 3-fixnum
2021-01-24 nuove cover
    nuove cover
2021-01-31 febbraio - 1
    febbraio - contapezzi e simili
2021-02-17 febb 2
    febb2
2021-02-19 fix nextion
    fix nextion
2021-03-03 marzo2021
    marzo2021 - inverter
2021-03-12 13mar21
    13mar21
2021-03-19 shield didattica
    shield didattica
2021-03-25 fine marzo
    fine marzo - can bus
2021-04-03 .
    .
2021-04-26 a
    a
2021-05-26 '
    '
2021-06-21 lora
    lora
2021-09-22 -
    .
2021-09-22 Create A592.pdf
    .
2022-03-31 corso base arduino
    copia codice corso base
2022-05-02 bootloader prog
    .
2022-05-10 live
    materiale live gps tracker
2022-05-14 iot proto shield
    .
2022-05-25 gps tracker
    tracker
2022-06-01 corso arduino avanzao
2022-06-14 aggiunta corso rete
    ,
2022-06-15 flussi, platformio
2022-07-08 fix secrets.h mancante
    fix secrets.h mancante
2022-09-23 pid
    pid
2022-09-27 live
    live
2022-10-21 ..
    ...
2022-10-21 .lìpid
    pid
2022-10-27 live 27 10
    interrupts
2022-11-08 bootloader
    ..
2022-11-15 pwm lento
    pwm lento
2022-11-24 live 24 nov
    ESP32 E BT
2022-12-02 live 1 dic
    .
2022-12-07 live 7 dic
    live spiffs
2022-12-22 ota e alexa base
    .
2023-01-05 mpu
    mpu
2023-03-01 433Mhz
    433
2023-03-02 .
    .live
2023-04-05 opta
    opta
2023-06-08 fix pdf
    fix pdf mosi pin
2023-07-22 luglio2023
    ..
2023-08-04 R4
    R4
2023-08-28 R4
    R4 e varie
2023-11-14 python
    upython
2023-11-27 Update main.py
    fix code
2023-11-29 esp32 diy
2023-12-07 fix ordine e natale
    albero natale
2023-12-07 fix numeri
    fix numrazione
2023-12-23 trash loop
    .
2023-12-28 fix cartelle
    ok
2023-12-29 cover
    cover
2024-01-17 add 7447 kicad
    .
2024-02-02 useless box
    .
2024-02-13 digipot
    digipot
2024-02-17 ch340
    driver
2024-02-21 corso r4
    .
2024-02-29 new videeo
2024-03-19 removed
    r
2024-04-18 crc
    crc
2024-04-28 lib e new vid
2024-05-02 json
2024-05-13 Create REST.pdf
    .
2024-05-13 server python
    py
2024-05-23 rest server
    .
2024-05-29 sql
    .
2024-06-06 mqtt
    mqtt
2024-06-22 Create millis-overflow.ino
    .
2024-06-27 clean sens info
2024-07-27 modulino
    plug and make
2024-08-03 modukino
2024-09-02 sprintf
    .
2024-09-09 printf
    .
2024-09-09 fix num
    .
2024-09-17 batteria
2024-09-30 sd
    sd
2024-09-30 sd fix
    err numerazione
2024-10-20 fix numerazione
2024-11-06 fix numb
2024-11-20 fix name
2024-11-22 vento e matrici
2024-11-29 clock
2024-12-04 fix matrix
2024-12-13 puntatori e ref
2025-01-10 esp32 reg
2025-01-17 FastPwm
2025-02-07 noob2pro
2025-02-07 schema
2025-02-22 mqtt
2025-02-28 influx
2025-03-14 dcf e influx
2025-03-14 opamp
2025-04-18 904-905
2025-05-02 sht20
2025-05-15 node red
2025-06-06 cambio numero
2025-06-07 3 task
2025-06-21 goertzel
2025-06-21 matrix neo
2025-06-28 elecrow
    .
2025-07-26 freertos
2025-09-10 lcd
    .
2025-09-10 optojfet
2025-09-25 938 fix
2025-10-09 sd e waveshare
2025-11-06 mos e miniplay
2025-11-10 karzuino?
2025-11-10 dfminiplayer
2025-11-14 pot dig
2025-11-27 live
2025-12-04 baricentro
2025-12-05 led parlante
2025-12-10 fix subfloder
2025-12-10 live 10/12
2025-12-20 alba-tramonto
2025-12-31 kalman
2026-02-01 plc elsist
2026-02-24 atecc
2026-02-27 fix atecc
2026-03-05 el nascosti
2026-03-07 atecc e secure button
2026-03-28 lm317 e wsp32pcnt
2026-04-17 plc e idf
2026-06-01 modulo relè
